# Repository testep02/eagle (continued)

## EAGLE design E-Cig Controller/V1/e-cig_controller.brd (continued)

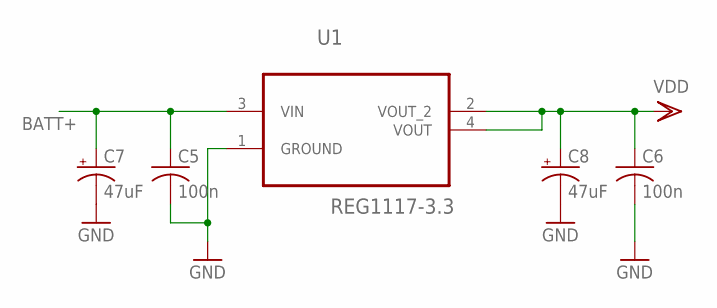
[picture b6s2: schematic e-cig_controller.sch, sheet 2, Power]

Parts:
C5, C6: 100n; C0603
C7, C8: 47uF; A/3216-18W
U1: REG1117-3.3; SOT230P700X180-4N

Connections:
BATT+: C5.1, C7.+, U1.3 (VIN); also elsewhere on the board
GND: C5.2, C6.2, C7.-, C8.-, U1.1 (GROUND); also elsewhere on the board
VDD: C6.1, C8.+, U1.2 (VOUT_2), U1.4 (VOUT)

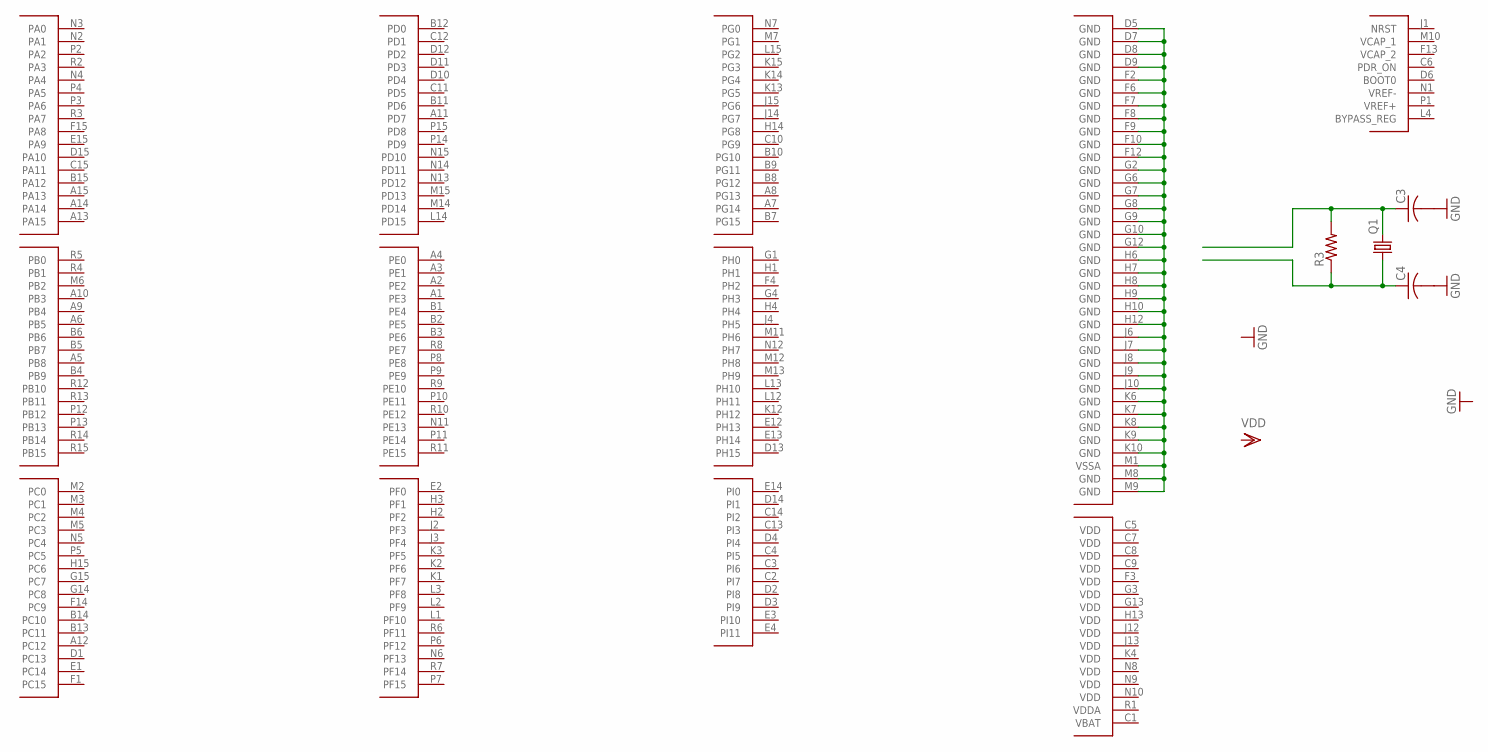
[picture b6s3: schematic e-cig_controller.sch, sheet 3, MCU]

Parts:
C3, C4: C-USC0603; C0603
Q1: CRYSTALHC49US; HC49US
R3: R-US_R0603; R0603
U$2: STM32F407IG; UFBGA176+25

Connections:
GND: C3.2, C4.2; also elsewhere on the board
unnamed: U$2.D5 (GND), U$2.D7 (GND), U$2.D8 (GND), U$2.D9 (GND), U$2.F2 (GND), U$2.F6 (GND), U$2.F7 (GND), U$2.F8 (GND), U$2.F9 (GND), U$2.F10 (GND), U$2.F12 (GND), U$2.G2 (GND), U$2.G6 (GND), U$2.G7 (GND), U$2.G8 (GND), U$2.G9 (GND), U$2.G10 (GND), U$2.G12 (GND), U$2.H6 (GND), U$2.H7 (GND), U$2.H8 (GND), U$2.H9 (GND), U$2.H10 (GND), U$2.H12 (GND), U$2.J6 (GND), U$2.J7 (GND), U$2.J8 (GND), U$2.J9 (GND), U$2.J10 (GND), U$2.K6 (GND), U$2.K7 (GND), U$2.K8 (GND), U$2.K9 (GND), U$2.K10 (GND), U$2.M1 (VSSA), U$2.M8 (GND), U$2.M9 (GND)
unnamed: C3.1, Q1.2, R3.2
unnamed: C4.1, Q1.1, R3.1

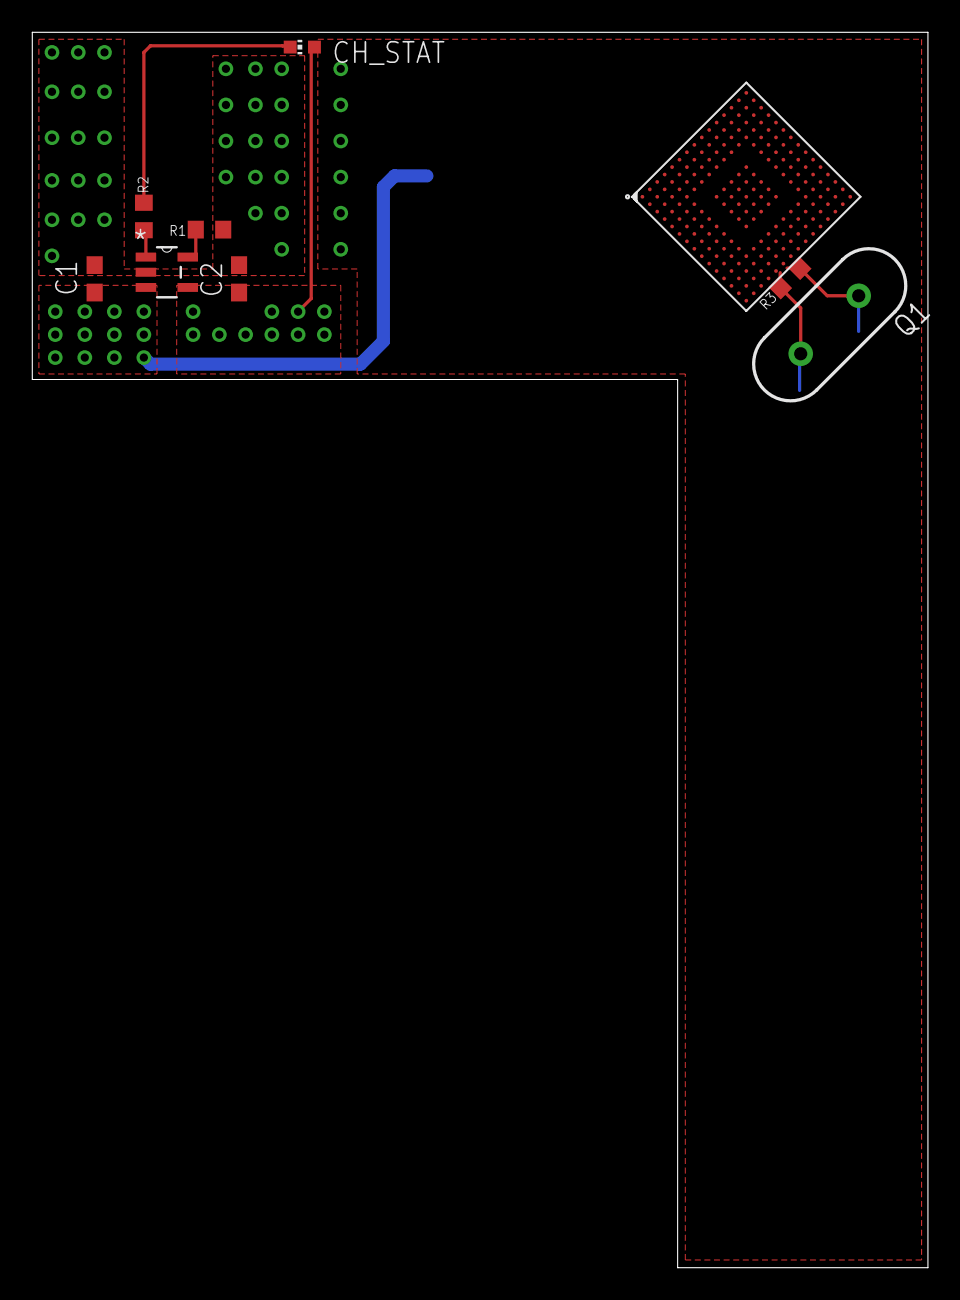
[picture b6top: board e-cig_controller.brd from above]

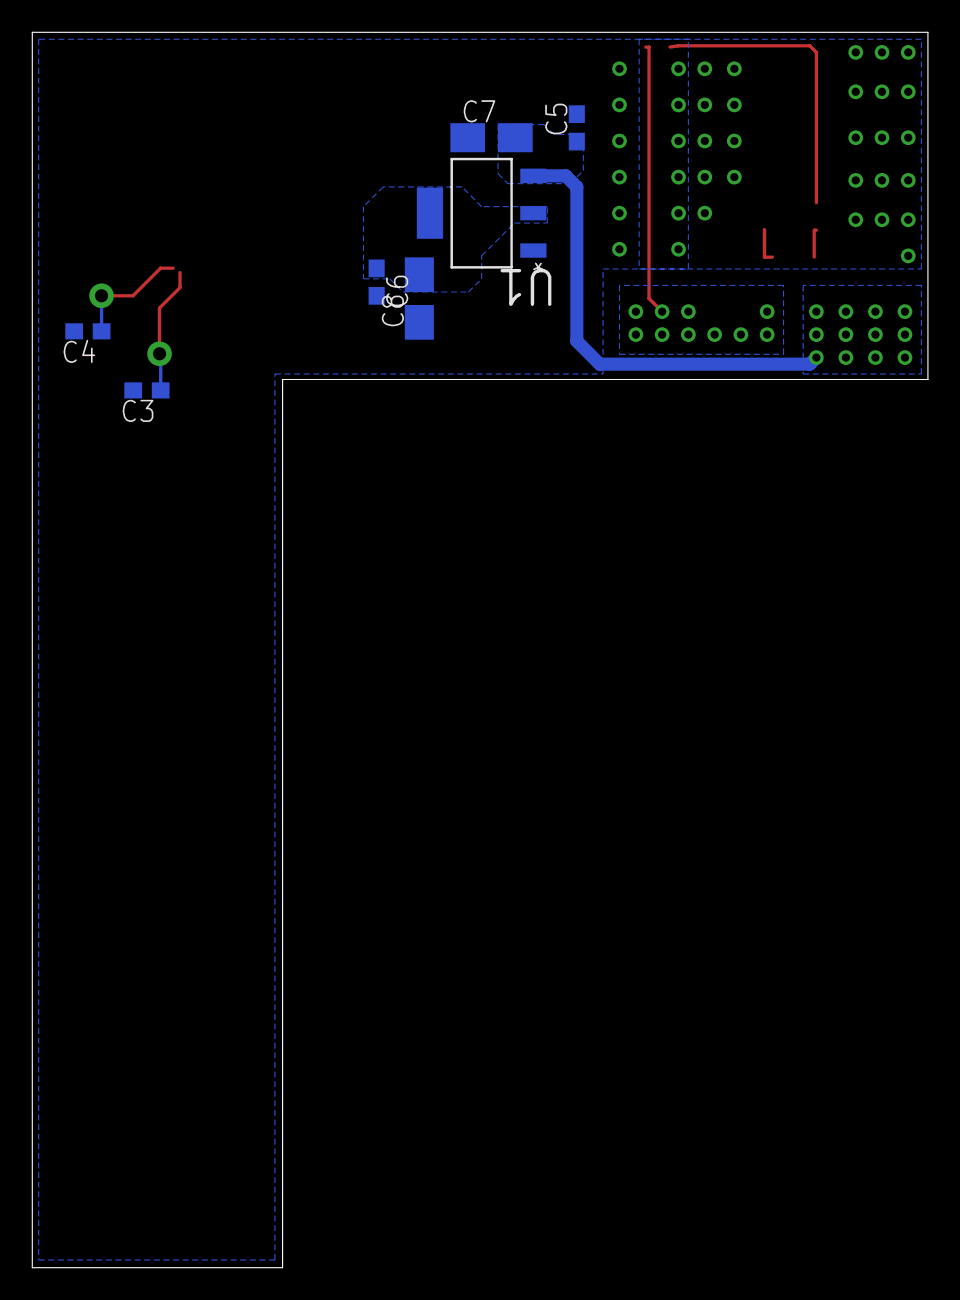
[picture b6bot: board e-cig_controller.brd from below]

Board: 2 copper layers, 55.5 x 76.5 mm, 16 parts (7 on the bottom side), 10 nets.
